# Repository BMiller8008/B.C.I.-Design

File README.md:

# B.C.I.-Design

Github for Team2 of Purdue's ECE477 Senior Design Class

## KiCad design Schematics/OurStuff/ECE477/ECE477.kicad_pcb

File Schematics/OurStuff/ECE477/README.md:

This is an example schematic from Ben Miller's Senior Design Team.

The board uses an ESP32, CP2102N usb-uart bridge, and a Pololu Buck Converter

I recomend using a EXTERNAL BRIDGE - to reduce complexity if hand soldering

If not hand holdering keep the bridge.

You also could use a LDO rather than a buck converter, but the buck will be more power efficient

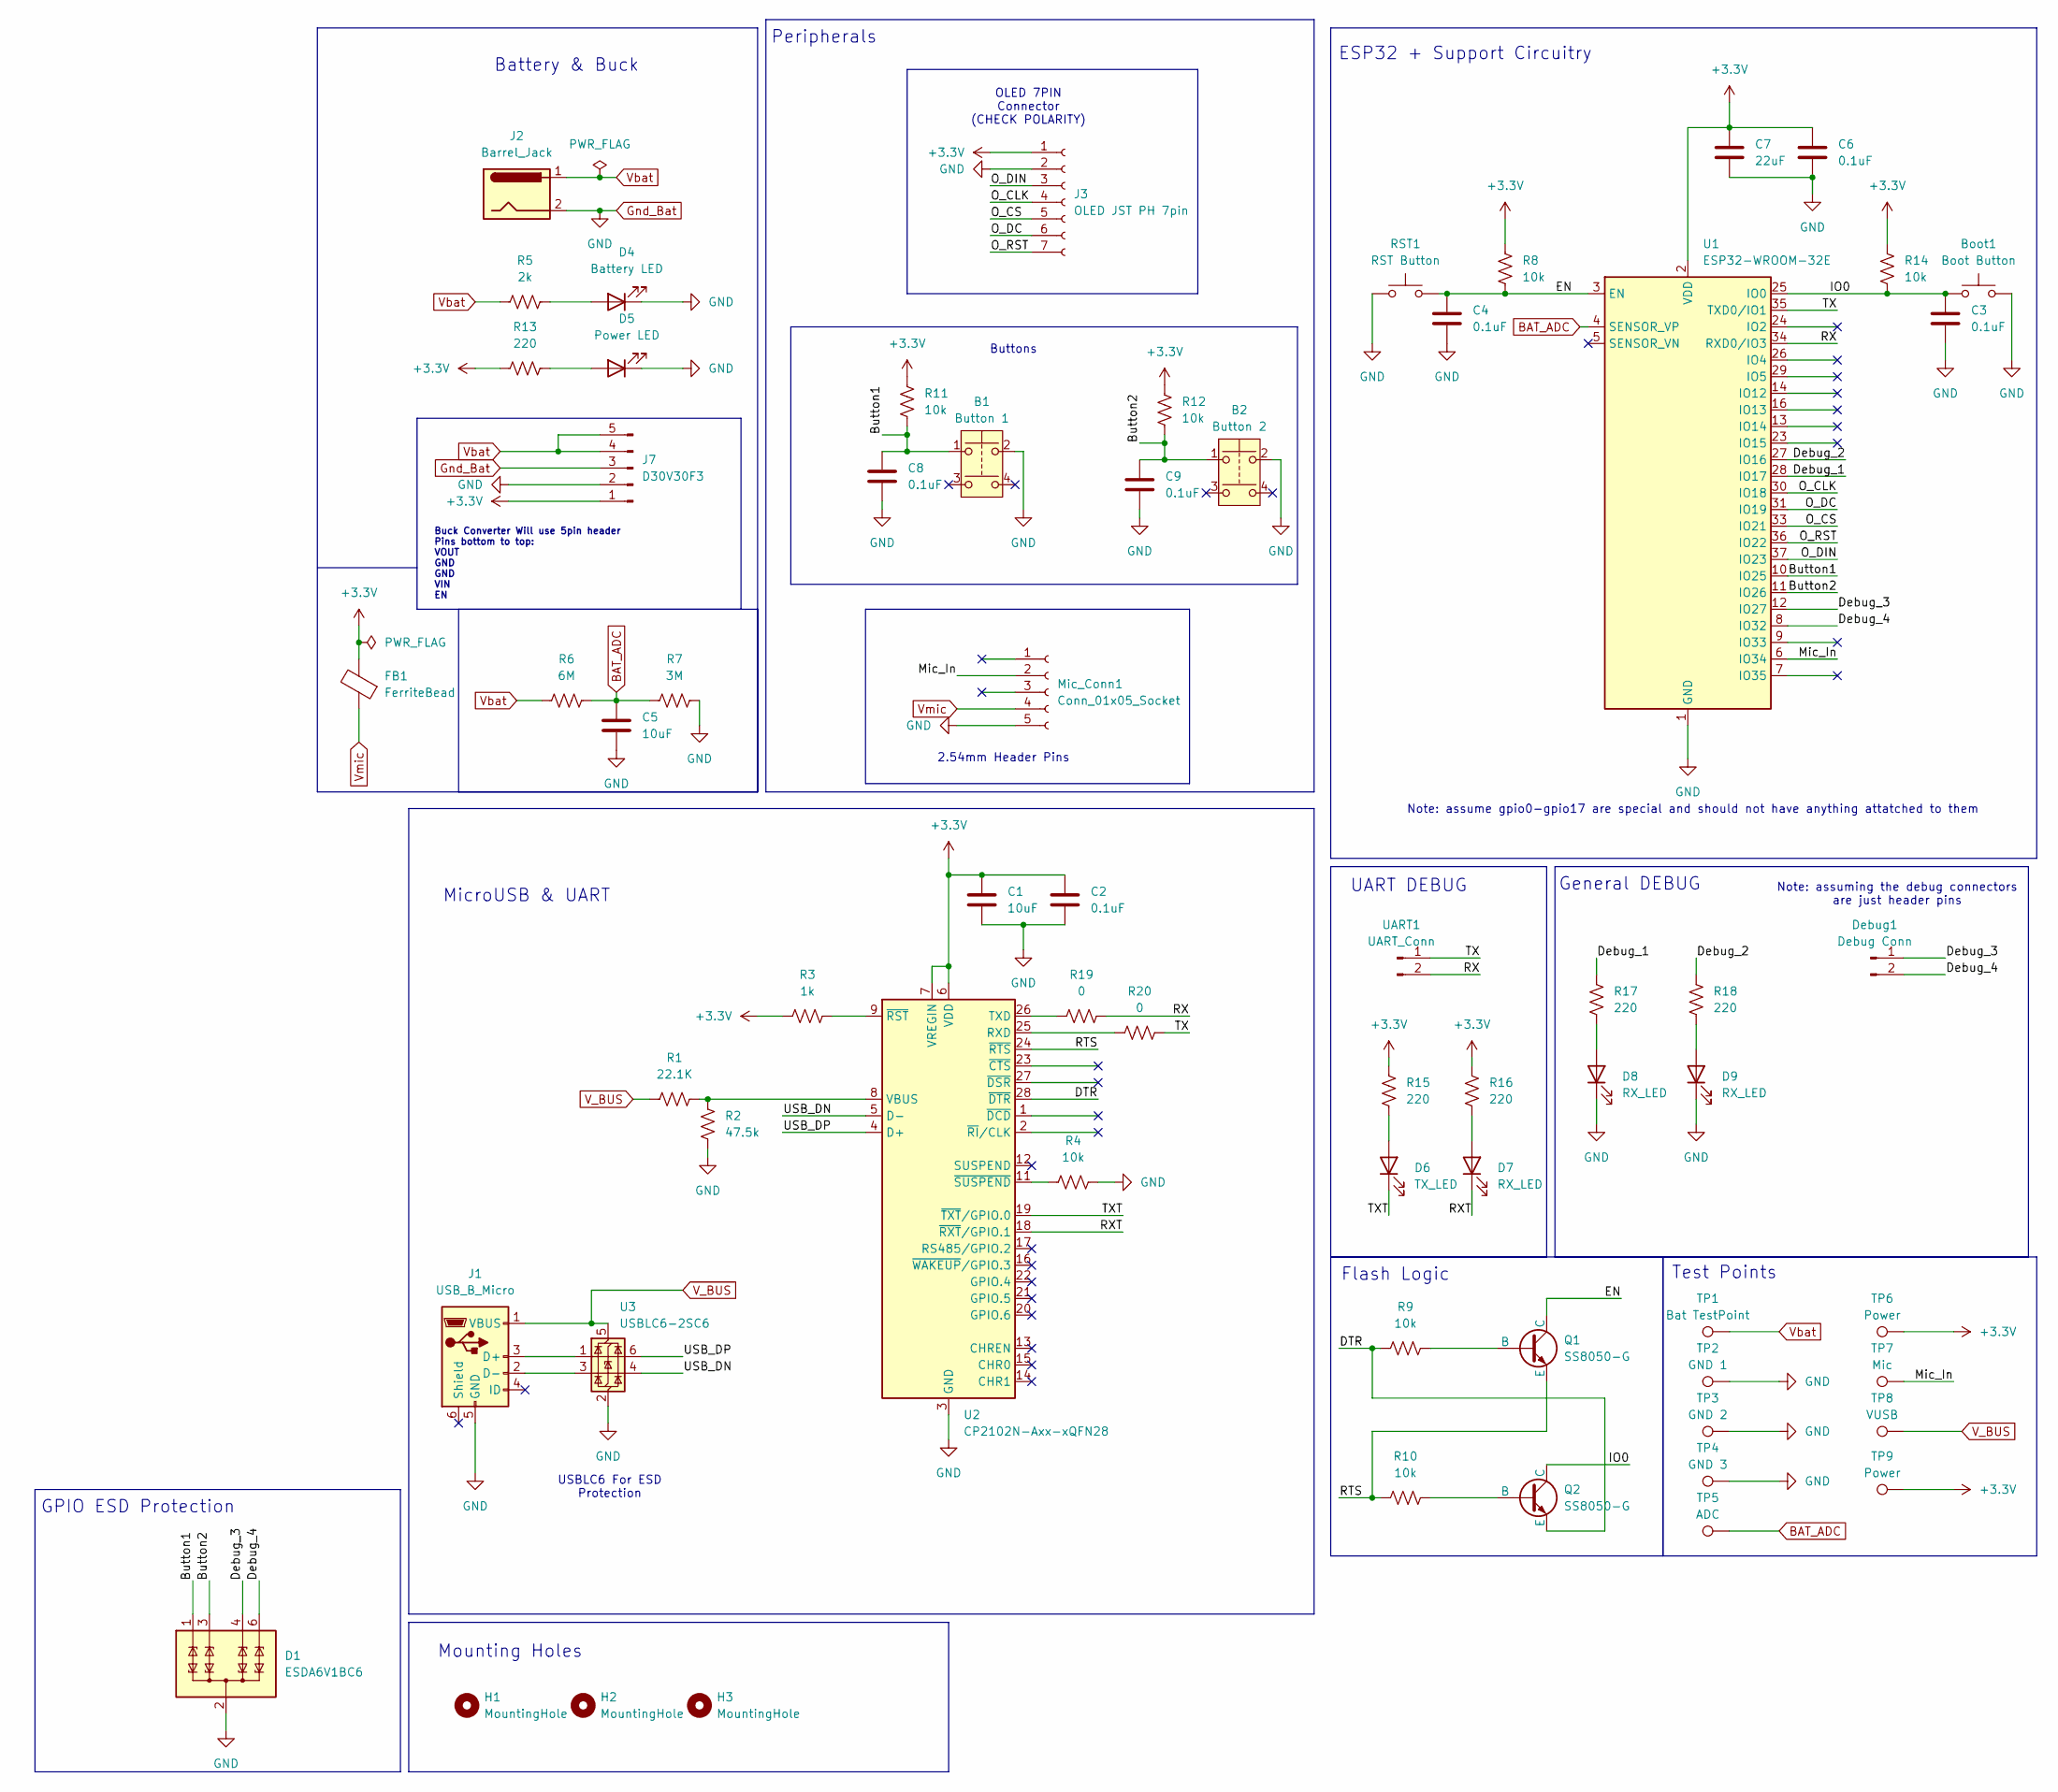
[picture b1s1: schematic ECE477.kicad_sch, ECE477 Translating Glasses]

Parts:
B1: Button 1; SW_PUSH_6mm_H13mm
B2: Button 2; SW_PUSH_6mm_H13mm
Boot1: Boot Button; SW_PUSH_1P1T_6x3.5mm_H4.3_APEM_MJTP1243
C1, C5: 10uF; C_0805_2012Metric_Pad1.18x1.45mm_HandSolder
C2, C3, C4, C6, C8, C9: 0.1uF; C_0805_2012Metric_Pad1.18x1.45mm_HandSolder
C7: 22uF; C_0805_2012Metric_Pad1.18x1.45mm_HandSolder
D1: ESDA6V1BC6; SOT-23-6
D4: Battery LED; LED_0805_2012Metric_Pad1.15x1.40mm_HandSolder
D5: Power LED; LED_0805_2012Metric_Pad1.15x1.40mm_HandSolder
D6: TX_LED; LED_0805_2012Metric_Pad1.15x1.40mm_HandSolder
D7, D8, D9: RX_LED; LED_0805_2012Metric_Pad1.15x1.40mm_HandSolder
Debug1: Debug Conn; PinHeader_1x02_P2.54mm_Vertical
FB1: FerriteBead; L_0805_2012Metric_Pad1.05x1.20mm_HandSolder
H1, H2, H3: MountingHole; MountingHole_2.5mm
J1: USB_B_Micro; USB_Micro-B_Wuerth_614105150721_Vertical
J2: Barrel_Jack; BarrelJack_Wuerth_6941xx301002
J3: OLED JST PH 7pin; JST_PH_B7B-PH-K_1x07_P2.00mm_Vertical
J7: D30V30F3; PinHeader_1x05_P2.54mm_Vertical
Mic_Conn1: Conn_01x05_Socket; PinHeader_1x05_P2.54mm_Vertical
Q1, Q2: SS8050-G; SOT-23
R1: 22.1K; R_0805_2012Metric_Pad1.20x1.40mm_HandSolder
R2: 47.5k; R_0805_2012Metric_Pad1.20x1.40mm_HandSolder
R3: 1k; R_0805_2012Metric_Pad1.20x1.40mm_HandSolder
R4, R8, R9, R10, R11, R12, R14: 10k; R_0805_2012Metric_Pad1.20x1.40mm_HandSolder
R5: 2k; R_0805_2012Metric_Pad1.20x1.40mm_HandSolder
R6: 6M; R_0805_2012Metric_Pad1.20x1.40mm_HandSolder
R7: 3M; R_0805_2012Metric_Pad1.20x1.40mm_HandSolder
R13, R15, R16, R17, R18: 220; R_0805_2012Metric_Pad1.20x1.40mm_HandSolder
R19, R20: 0; R_0805_2012Metric_Pad1.20x1.40mm_HandSolder
RST1: RST Button; SW_PUSH_1P1T_6x3.5mm_H4.3_APEM_MJTP1243
TP1: Bat TestPoint; TestPoint_Keystone_5010-5014_Multipurpose
TP2: GND 1; TestPoint_Keystone_5010-5014_Multipurpose
TP3: GND 2; TestPoint_Keystone_5010-5014_Multipurpose
TP4: GND 3; TestPoint_Keystone_5010-5014_Multipurpose
TP5: ADC; TestPoint_Keystone_5010-5014_Multipurpose
TP6, TP9: Power; TestPoint_Keystone_5010-5014_Multipurpose
TP7: Mic; TestPoint_Keystone_5010-5014_Multipurpose
TP8: VUSB; TestPoint_Keystone_5010-5014_Multipurpose
U1: ESP32-WROOM-32E; ESP32-WROOM-32D
U2: CP2102N-Axx-xQFN28; QFN-28-1EP_5x5mm_P0.5mm_EP3.35x3.35mm
U3: USBLC6-2SC6; SOT-23-6
UART1: UART_Conn; PinHeader_1x02_P2.54mm_Vertical

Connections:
+3.3V: C1.1, C2.1, C6.1, C7.1, FB1.2, J3.1, J7.1, R3.2, R8.2, R11.1, R12.1, R13.1, R14.2, R15.1, R16.1, TP6.1, TP9.1, U1.2 (VDD), U2.6 (VDD), U2.7 (VREGIN)
/Button1: B1.1, C8.1, D1.1 (TVS1), R11.2, U1.10 (IO25)
/Button2: B2.1, C9.1, D1.3 (TVS2), R12.2, U1.11 (IO26)
/DTR: Q2.3 (E), R9.2, U2.28 (~DTR)
/Debug_1: R17.1, U1.28 (IO17)
/Debug_2: R18.1, U1.27 (IO16)
/Debug_3: D1.4 (TVS3), Debug1.1, U1.12 (IO27)
/Debug_4: D1.6 (TVS4), Debug1.2, U1.8 (IO32)
/EN: C4.1, Q1.1 (C), R8.1, RST1.2, U1.3 (EN)
/IO0: Boot1.1, C3.2, Q2.1 (C), R14.1, U1.25 (IO0)
/Mic_In: Mic_Conn1.2, TP7.1, U1.6 (IO34)
/O_CLK: J3.4, U1.30 (IO18)
/O_CS: J3.5, U1.33 (IO21)
/O_DC: J3.6, U1.31 (IO19)
/O_DIN: J3.3, U1.37 (IO23)
/O_RST: J3.7, U1.36 (IO22)
/RTS: Q1.3 (E), R10.2, U2.24 (~RTS)
/RX: R19.1, U1.34 (RXD0/IO3), UART1.2
/RXT: D7.1 (K), U2.18 (~RXT/GPIO.1)
/TX: R20.1, U1.35 (TXD0/IO1), UART1.1
/TXT: D6.1 (K), U2.19 (~TXT/GPIO.0)
/USB_DN: U2.5 (D-), U3.4 (I/O2)
/USB_DP: U2.4 (D+), U3.6 (I/O1)
BAT_ADC: C5.1, R6.2, R7.1, TP5.1, U1.4 (SENSOR_VP)
Gnd_Bat: B1.2, B2.2, Boot1.2, C1.2, C2.2, C3.1, C4.2, C5.2, C6.2, C7.2, C8.2, C9.2, D1.2 (COM), D1.5 (COM), D4.1 (K), D5.1 (K), D8.1 (K), D9.1 (K), J1.5 (GND), J2.2, J3.2, J7.2, J7.3, Mic_Conn1.5, R2.2, R4.1, R7.2, RST1.1, TP2.1, TP3.1, TP4.1, U1.1 (GND), U1.15 (GND), U1.38 (GND), U1.39 (GND), U2.3 (GND), U2.29 (GND), U3.2 (GND)
unnamed: D4.2 (A), R5.2
unnamed: D5.2 (A), R13.2
unnamed: D6.2 (A), R15.2
unnamed: D7.2 (A), R16.2
unnamed: D8.2 (A), R17.2
unnamed: D9.2 (A), R18.2
unnamed: J1.3 (D+), U3.1 (I/O1)
unnamed: J1.2 (D-), U3.3 (I/O2)
unnamed: Q1.2 (B), R9.1
unnamed: Q2.2 (B), R10.1
unnamed: R20.2, U2.25 (RXD)
unnamed: R19.2, U2.26 (TXD)
unnamed: R1.1, R2.1, U2.8 (VBUS)
unnamed: R3.1, U2.9 (~RST)
unnamed: R4.2, U2.11 (~SUSPEND)
V_BUS: J1.1 (VBUS), R1.2, TP8.1, U3.5 (VBUS)
Vbat: J2.1, J7.4, J7.5, R5.1, R6.1, TP1.1
Vmic: FB1.1, Mic_Conn1.4

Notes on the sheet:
Buttons
Note: assume gpio0-gpio17 are special and should not have anything attatched to them
Note: assuming the debug connectors are just header pins
USBLC6 For ESD Protection
UART DEBUG
Peripherals
Mounting Holes
MicroUSB & UART
OLED 7PIN Connector (CHECK POLARITY)
Test Points
GPIO ESD Protection
General DEBUG
2.54mm Header Pins
ESP32 + Support Circuitry
Buck Converter Will use 5pin header Pins bottom to top: VOUT GND GND VIN EN
Battery & Buck
Flash Logic

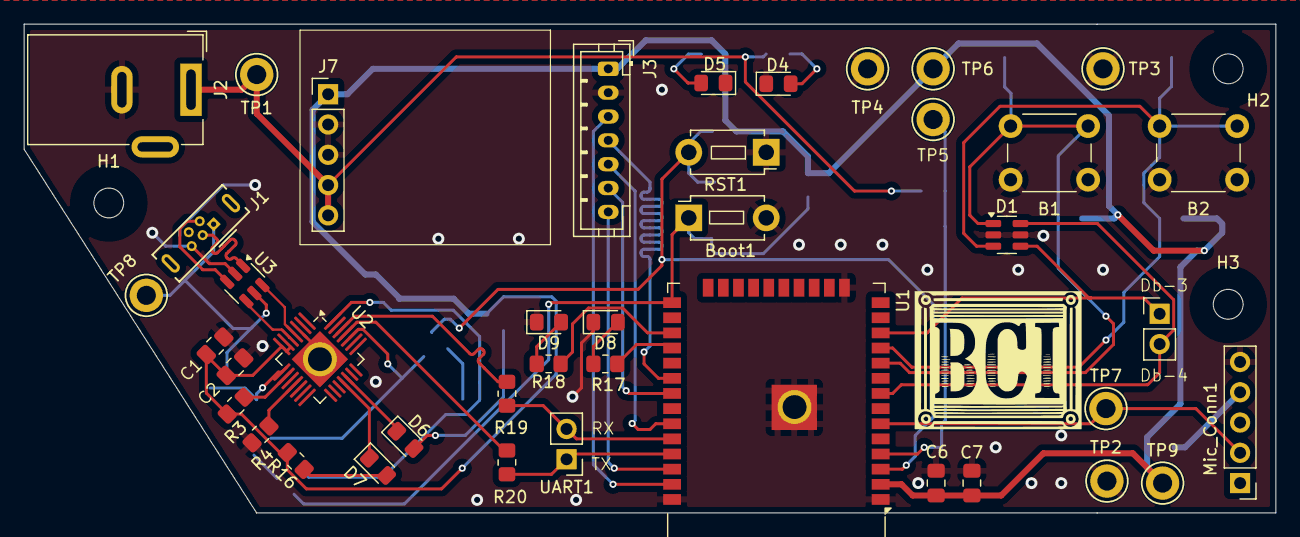
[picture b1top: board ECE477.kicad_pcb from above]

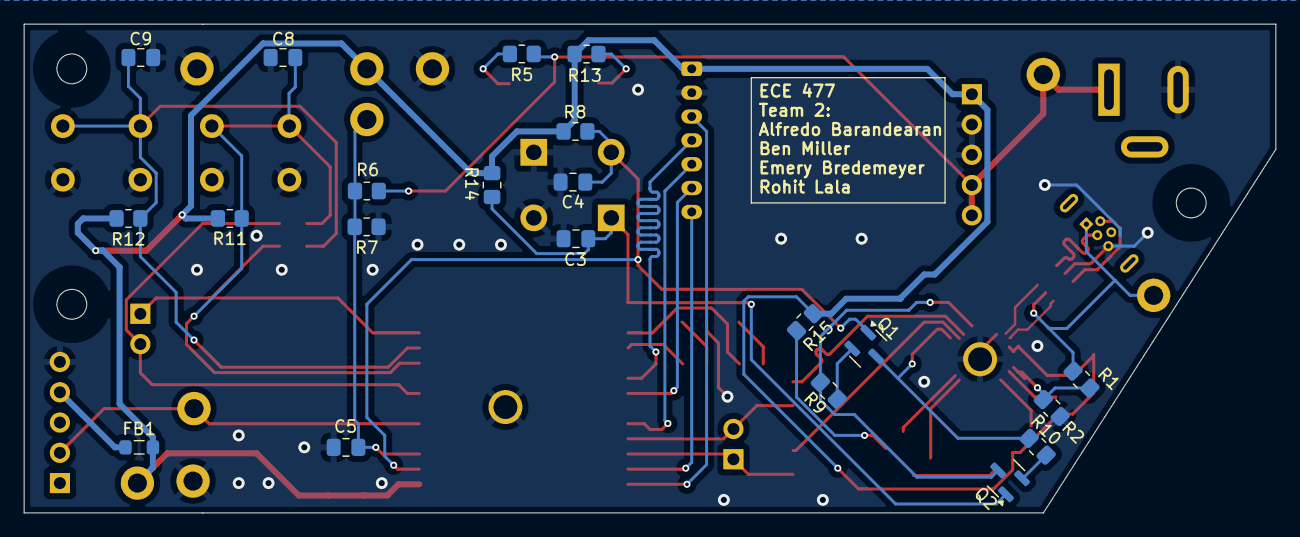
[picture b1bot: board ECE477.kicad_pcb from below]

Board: 2 copper layers, 105.0 x 41.0 mm, 65 parts (21 on the bottom side), 43 nets.

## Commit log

2025-01-15 initial website
2025-01-22 add rough directory structure
2025-01-22 setup esp project
2025-01-22 renamed template
2025-01-23 created timer example
2025-01-23 created blink example
2025-01-28 Started Writing Wifi Library
2025-01-29 uploaded example schematics
2025-01-29 Started Sender Task
2025-01-30 got basic communication working
2025-01-30 Updated Server
2025-01-30 Added receiver task and cleaned up
2025-01-31 Added OLED Library
2025-02-03 InitialOLED Library Complete
2025-02-04 completed basic OLED class
2025-02-05 skeleton example for the ringbuffereing audio
2025-02-10 Started Schematics
2025-02-10 fixed power
2025-02-11 Finished UART
2025-02-11 created symbol
2025-02-14 Fixed config
2025-02-15 added auto flash circuitry
2025-02-18 Added Peripherals
2025-02-18 add original working (unimproved) battery indicator
2025-02-18 updated battery indicator
2025-02-19 added debug
2025-02-19 fixed issues
2025-02-19 began footprinting
2025-02-19 aaaa
2025-02-20 fixed mistakes & almost finished footprints
2025-02-20 delteing setup passive files i dont need
2025-02-21 added test points and mounting holes
2025-02-21 Started layout
2025-02-21 started routing 💢
2025-02-25 finished pcb layout v1
2025-02-26 pre deletion
    pre deleted ver in case of misshap
2025-02-26 ver 2 before delete
2025-02-26 battery indicator displaying on oled
2025-02-27 hell yeah
    pcb complete ver 1 (no more deletes please)
2025-02-27 fixed footprints
2025-03-01 swapped ESD protection on schematic
2025-03-01 updated PCB with new ESD IC
2025-03-01 revised changes from dr W feedback
    hi
2025-03-04 added bat mon capacitor
2025-03-04 added logo
2025-03-04 micrphone code
    code with fir filter and a plotter
    no compression
2025-03-05 added basic mic code and added send_raw()
2025-03-10 added ferrite bead and fixed mic
2025-03-10 acute angle and added via
2025-03-12 added power label
2025-03-13 fixed sampling gayness
2025-03-13 added python filtering
2025-03-13 updated PCB with suggestions 1-4
2025-03-26 cleaned up
    switched to TCP for receiving
2025-03-26 added timeout support
2025-03-26 added command sender
2025-03-28 created main class
2025-04-02 live_transaltion
2025-04-02 started WIFI intergration
2025-04-02 intergrated wifimanager and mic into main
2025-04-02 intergrated OLED and WIFI
2025-04-02 multithread try 1
2025-04-02 temp
2025-04-02 temp 2
2025-04-02 kinda working
2025-04-02 WORKED EXCEPT DISPLAY
2025-04-02 Got it working
2025-04-03 addded menu code
2025-04-04 temp
    int temp
2025-04-04 comments
    added comments
2025-04-04 added buttons receiving side
2025-04-05 started buttons
2025-04-07 menus + buttons
2025-04-08 cleaned code for real hardware
2025-04-09 working code!!!!
2025-04-09 added ADC and font code
2025-04-09 Pre Demo
2025-04-10 fw Translation + auto IP
2025-04-10 Demo Config
2025-04-16 added support for flipped text
2025-04-21 fixed font issue
2025-04-22 removed long press
2025-04-30 fixed double presses
2025-05-01 add requriements for server
